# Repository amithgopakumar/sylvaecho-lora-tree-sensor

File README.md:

# SylvaEcho

A solar-powered LoRa sensor that straps to a tree trunk. It listens for pollinators and birds, detects illegal logging, and reports when a tree or slope starts to lean. It runs without mobile coverage, for forest departments, researchers, farms and citizen scientists.

This is an open hardware project for the [EasyEDA Spark 2026](https://oshwlab.com/activities/easyeda-spark-2026) competition. The PCB is designed in EasyEDA Pro.

## What it does

- **Biodiversity by sound.** Every 30 minutes the node wakes for 10 seconds, powers its microphone and scores pollinator buzz (150–400 Hz) and bird activity (1–6 kHz) on the nRF52840.
- **Illegal logging alerts.** A piezo disc on the trunk plate feeds a band-pass filter and a nanopower comparator. Sustained trunk vibration wakes the MCU, which then checks the IMU and three 1-second audio clips for a chainsaw. An alert is sent only when both agree, which cuts false alarms from wind, rain and traffic.
- **Tilt monitoring.** The IMU tracks slow tilt from cutting, tree fall or soil creep.
- **Long range, no SIM.** Reports and alerts go out over LoRa (IN865, EU868 or US915).
- **Sealed setup.** An NFC tap wakes Bluetooth for configuration, so the enclosure never needs opening.

Between listening windows the microphone rail is switched off. The design target is an average current of about 115 µA.

## Hardware

| Function | Part |
|---|---|
| MCU + Bluetooth | Seeed XIAO nRF52840 |
| LoRa radio | Seeed Wio-SX1262 SMT module, up to +22 dBm, U.FL antenna |
| Microphone | Knowles SPH0641LU4H-1 PDM MEMS microphone (bottom port) |
| Motion / tilt | ST LSM6DSOX 6-axis IMU |
| Environment | Bosch BME680 on rev 0.4, BME280 on rev 0.3 (temperature, humidity, pressure) |
| Trunk vibration wake | Piezo disc + TLV7041 nanopower comparator |
| Solar harvesting | TI BQ25570 with MPPT, charging one LiFePO4 cell |
| 3.3 V supply | TI TPS63900 buck-boost |
| I/O expander | TI TCA9534 |
| Mic power switch | TI TPS22917 load switch |
| Expansion | Qwiic (JST-SH) I2C port, test points |

The board is 4-layer, 60 × 45 mm, 1.6 mm FR-4.

### Board versions

The two versions differ only in the environment sensor U5. Both sensors use the same pin order and the same I2C address (0x76), so the schematic, firmware and LoRa report are the same.

| Version | U5 | LCSC part | Footprint | Files |
|---|---|---|---|---|
| Rev 0.4 (current) | Bosch BME680 | C125972 | LGA-8, 3.0 × 3.0 mm, 0.8 mm pitch | `PCB/BME680_rev0.4/` |
| Rev 0.3 | Bosch BME280 | C92489 | LGA-8, 2.5 × 2.5 mm, 0.65 mm pitch | `PCB/BME280_rev0.3/` |

Rev 0.4 was made because the BME280 went out of stock at JLCPCB. The BME680 also has a gas (VOC) sensor; the firmware reads only temperature, humidity and pressure from it.

### Solar panel and battery

- **Battery:** one LiFePO4 cell, for example an IFR18500 (the enclosure size) or an IFR18650. The charger stops at 3.51 V and the system cuts off at about 2.8 V.
- **Solar panel:** 0.3–0.5 W with an open-circuit voltage (Voc) **below 3.1 V**. A 4-cell panel sold as "2 V" (Voc around 2.4–2.6 V) fits. Panels sold as "3 V" usually have a Voc of 3.5–3.6 V, which is too high for this charger setting.

## Companion board SC-1 (battery gauge, security, field sensors)

Rev 0.4 has no battery-voltage line to the MCU, so it cannot report how full the cell is. SC-1 fixes that without changing the main board: it plugs into the Qwiic port, and the battery and piezo cables pass through it.

| Block | Parts | What it does |
|---|---|---|
| Battery gauge | INA219 + 0.22 Ω shunt, ATtiny1616 | Battery voltage and current both ways; charge counting gives the battery % (corrected from the resting voltage at night) |
| Security | ATECC608B | Per-node key that cannot be read out; monotonic counter against replayed packets |
| Field sensors | 5-pin JST-PH: soil-moisture probe, soil NTC, rain gauge; 2-pin cell NTC | Landslide (slope-risk) index together with the main board tilt |
| Trunk sound | MCP6001, 0.5–3.4 kHz, gain 101 | Night listening for wood-boring larvae (red palm weevil) |

- I2C addresses on the main bus: ATtiny1616 0x2A, ATECC608B 0x60. The INA219 sits on the ATtiny's private bus and is powered only while sampling.
- 46 × 21 mm, 2 layers. ICs and connectors on top, 0805 passives on the bottom: everything is hand-solderable.
- Program the ATtiny over UPDI (J9) with a USB-serial adapter (SerialUPDI).
- Files: `PCB/Companion_SC1/` (EasyEDA Pro project, fabrication files, KiCad source and the scripts that generate it).
- v0.2 layout: passives spread with routing channels, every GND pad has its own via to the GND pours, signals routed with EasyEDA's JRouter. Schematic and PCB are linked (all 48 footprints assigned) and EasyEDA's DRC reports no issues.

## Repository layout

```
PCB/
  BME680_rev0.4/
    easyeda/      EasyEDA Pro project, rev 0.4 (schematic and routed PCB)
    fabrication/  Gerber files, JLCPCB BOM and pick-and-place files
  BME280_rev0.3/
    easyeda/      EasyEDA Pro project, rev 0.3
    fabrication/  Gerber files, JLCPCB BOM and pick-and-place files
  Companion_SC1/
    easyeda/      EasyEDA Pro project (.epro2) for the SC-1 add-on board
    fabrication/  Gerber files and the hand-solder BOM
    kicad_source/ Generated KiCad schematic/PCB and schematic PDF
    tools/        Generators and EasyEDA scripts used to build it
  footprints/     Custom KiCad footprints (XIAO SMD, mic, jumper, test point, mounting hole)
  schematic/      Original KiCad schematic (BME280), netlist, BOM and PDF
Firmware/         Zephyr firmware for the XIAO nRF52840 node (both board versions)
  variants/       Environment sensor overlay for each board version
SC1_Firmware/     ATtiny1616 co-processor firmware for the SC-1 add-on (PlatformIO)
Gateway/          XIAO ESP32S3 + Wio-SX1262 gateway: LoRa to USB serial, MQTT and HTTP (PlatformIO, Arduino)
Gateway_zephyr/   Same gateway on Zephyr RTOS: LoRa to USB serial and MQTT (shares Gateway/src/decode.cpp)
Dashboard/
  backend/        Python FastAPI + SQLite: ingest (HTTP/MQTT), history, alerts, settings, live WebSocket
  frontend/       Next.js "Canopy" dashboard: spatial glass UI over the forest
Images/           Renders, block diagram and schematic preview
```

## Building the firmware

The firmware uses Zephyr (nRF Connect SDK).

```
west build -b xiao_ble/nrf52840 Firmware
west flash
```

This builds for rev 0.4 (BME680). For a rev 0.3 board (BME280):

```
west build -b xiao_ble/nrf52840 Firmware -- -DSENSOR=bme280
```

Run `west build -p` after switching between the two so the build directory is regenerated.

Schedule, detection thresholds and LoRa settings are in `Firmware/src/config.h`. The default LoRa channel is 865.0625 MHz (IN865); change it for EU868 or US915. Logs go out over Segger RTT, because the UART pins are used by the microphone.

The node finds the SC-1 add-on at boot (I2C 0x2A) and works the same without it. With SC-1 fitted, every report carries a 24-byte extension (battery, cell and soil temperature, soil moisture, rain totals, borer index), and an SC-1 pulse on WAKE_N (optional TP1 to TP6 wire) sends a `sc1_alert` report for heavy rain, low battery or borer activity.

### SC-1 co-processor (ATtiny1616)

```
cd SC1_Firmware
pio run                                                 # build
pio run -t upload --upload-port /dev/cu.usbserial-XXXX  # flash over UPDI (J9)
```

Flash it with SerialUPDI: a 3.3 V USB-serial adapter with a 4.7k resistor from TX to RX, RX to J9 pin 1 (UPDI), plus 3V3 and GND. The register map is in `SC1_Firmware/src/sc1_regs.h` (the node uses an identical copy). Defaults, all changeable over I2C and saved with command 0xA5: 1000 mAh cell, battery sampled every 60 s, soil and NTCs every 30 min, rain alert at 50 tips (10 mm) per hour, low battery at 15 %, borer listen 20 s after each node report.

Battery % is a coulomb count from INA219 samples, reset at full charge and corrected from the resting LiFePO4 voltage near empty and full. The INA219 is powered only while sampling, so short LoRa transmit peaks between samples are missed; treat the % as an estimate until it has been checked against a bench discharge.

### Gateway (XIAO ESP32S3 + Wio-SX1262)

```
cd Gateway
cp src/secrets.example.h src/secrets.h   # Wi-Fi, MQTT broker and/or HTTP URL
pio run -t upload
pio device monitor                       # one JSON line per packet
```

It listens on the same channel as the node (865.0625 MHz, SF10, BW 125 kHz, CR 4/5, private sync word) and drops repeated packets by node and sequence number. Each report is printed on USB serial, published to MQTT as `sylvaecho/<node>/<type>`, and/or POSTed as JSON to `HTTP_URL`. Leave the MQTT host and HTTP URL empty for serial output only.

### Gateway on Zephyr (alternative)

```
cp Gateway_zephyr/secrets.conf.example Gateway_zephyr/secrets.conf   # Wi-Fi and MQTT
west build -b xiao_esp32s3/esp32s3/procpu Gateway_zephyr
west blobs fetch hal_espressif      # once, for the ESP32 Wi-Fi driver
west flash
```

Same radio settings, JSON output and MQTT topics as the Arduino gateway, using Zephyr's own SX1262 driver (`lora_recv_async`), Wi-Fi management, DHCP and MQTT client. It has no HTTP POST yet. Pins are in `Gateway_zephyr/boards/xiao_esp32s3_esp32s3_procpu.overlay`.

### Report format

19-byte base report (unchanged), with byte 18 = extension flags. When bit 0 is set, the 24-byte SC-1 block follows (43 bytes in total). The full layout is in `Firmware/src/payload.h`; the gateway decoder is `Gateway/src/decode.cpp`.

## Dashboard

```
cd Dashboard/backend
python3 -m venv .venv && .venv/bin/pip install -r requirements.txt
DEMO=1 .venv/bin/uvicorn app:app --port 8000     # DEMO=1 simulates three trees

cd Dashboard/frontend
npm install && npm run dev                      # http://localhost:3000
```

The backend stores every report in SQLite and pushes it to the browser over a WebSocket. Reports arrive from the Arduino gateway's HTTP POST (`HTTP_URL = "http://<pc>:8000/api/ingest"`, optional `INGEST_TOKEN`) or from MQTT (`MQTT_HOST=<broker>` subscribes to `sylvaecho/+/+`, which works with both gateways). Demo data is labelled "Demo data" in the corner and `"demo": true` in the API; leave `DEMO` unset for real nodes.

The front end is a spatial glass window over the forest photo, with mouse parallax and a fluid 1440 x 810 layout (a stacked layout on phones):

- **Tabs:** all trees, or one tree each. Switching wipes the node view and rolls the card titles.
- **Rail:** what the dial shows: slope risk, rain, battery, bird activity, temperature.
- **Dial:** the live value as a mint arc. Drag the white knob to set that metric's alert level (saved on the server). The centre button mutes alerts on this screen.
- **Node view:** the device photo with a live spectrogram drawn from the pollinator, bird and chainsaw scores. Click it to fill the window.
- **Storm watch:** tightens the rain and risk alerts and switches to the rain view.
- **Chainsaw guard:** arm or disarm alerts. A confirmed logging alert turns the card red.
- **Battery:** the SC-1 state of charge, current and cell temperature.
- **Timeline:** drag back through the last day. The forest behind the glass darkens for night hours.
- **Soundscape:** steps through recent highlights: dawn chorus, pollinators, rain, borer clicks and alerts.

Open `http://localhost:3000/?shot` for a flat, still layout for screenshots.

### Security and alerts

- **Signed reports.** Each node signs every packet. It adds a 16-byte trailer: a random boot ID, a counter, and an 8-byte HMAC-SHA256 tag (`Firmware/src/auth.c`). Give each node its own key: put it in `Firmware/secrets.conf` (copy `secrets.conf.example`) and put the same key in `Dashboard/backend/keys.json` (see `keys.example.json`). Both files are git-ignored.
- **What the server does.** The gateway passes the raw packet through, and the server checks the tag against the raw bytes (`Dashboard/backend/protocol.py`). For any node that has a key, it rejects:
  - unsigned packets (HTTP 403);
  - forged or altered packets (403);
  - replayed packets (409): a counter it has already seen, or a packet from an earlier boot.

  Each rejection is logged at `/api/security`, appears on the dashboard as a warning and in the soundscape, and sends a phone alert.
- **Test it.** `.venv/bin/python tools/attack_test.py --node 1` replays, forges and strips a real packet and shows the server rejecting each one. The demo trees sign with fixed, public demo keys; never use those on real nodes.
- **Phone alerts.** Set `NTFY_URL=https://ntfy.sh/<long-random-topic>` (or your own ntfy server, with `NTFY_TOKEN`) and subscribe to the same topic in the ntfy app. You get alerts for:
  - a confirmed chainsaw (while the guard is armed);
  - tree tilt;
  - SC-1 rain, low battery or borer alerts;
  - slope risk crossing its alert level;
  - rejected packets.

  Each kind of alert repeats at most every 10 minutes per tree.
- **Login.** Set `DASH_PASSWORD` to require a password for the dashboard, its API and the live socket. Sign-in tokens last 7 days. `INGEST_TOKEN` separately protects the gateway's `/api/ingest`.
- **HTTPS.** `Dashboard/Caddyfile` serves the dashboard, API and live socket on one HTTPS address. Build the front end with `NEXT_PUBLIC_API=same-origin`. The Caddyfile has not been tested here.
- **Not done yet.** The key is still in node flash. Next step: keep it in the ATECC608B on SC-1 and use its HMAC command and monotonic counter.

The slope-risk index (0-100) combines 24 h and 3-day rain, soil moisture and tree tilt. It is a screening heuristic for the dashboard, not a calibrated landslide model.

## Ordering the board

1. Open `PCB/BME680_rev0.4/easyeda/SylvaEcho_rev0.4_BME680.epro` in EasyEDA Pro (File > Import), or use the files in `PCB/BME680_rev0.4/fabrication/` directly. For the BME280 version use `PCB/BME280_rev0.3/`.
2. PCB: 4 layers, 1.6 mm, lead-free HASL.
3. Assembly (Standard PCBA, top side): upload the `JLC_BOM_*.csv` and `JLC_CPL_*.csv` files from the same folder. JLCPCB flags the SPH0641 microphone (U7) for a manual review after the order is placed.
4. Hand-solder the XIAO nRF52840 (M1) and the Wio-SX1262 module (M2) after assembly. C11 and C12 are optional antenna-matching parts and are not fitted by default.

## Status

| Item | State |
|---|---|
| Schematic | Rev 0.3 |
| PCB layout | Rev 0.4 (BME680) routed and DRC checked; rev 0.3 (BME280) kept |
| Prototype boards | Rev 0.4 at JLCPCB (5 PCBs, 2 assembled); Spark sponsorship coupon approved |
| Companion board SC-1 | v0.2: routed, DRC clean; 5 PCBs and parts ordered (Lion Circuits, Robu, Evelta), boards due early December 2026 |
| MVP | Being built on development boards with the same sensors |
| Firmware | Node: first version plus SC-1 support; detection thresholds are placeholders until the classifier is trained |
| SC-1 firmware | Builds (8.2 KB of 16 KB flash); waiting for boards to test on hardware |
| Gateway firmware | Arduino version builds for the XIAO ESP32S3; decoder checked against the node's packer on a PC. Zephyr version written, not yet built |
| Dashboard | Python backend and Next.js front end run with demo data; waiting for the gateway to feed real reports |
| Field test | Planned |

## License

Apache License 2.0. See [LICENSE](LICENSE).

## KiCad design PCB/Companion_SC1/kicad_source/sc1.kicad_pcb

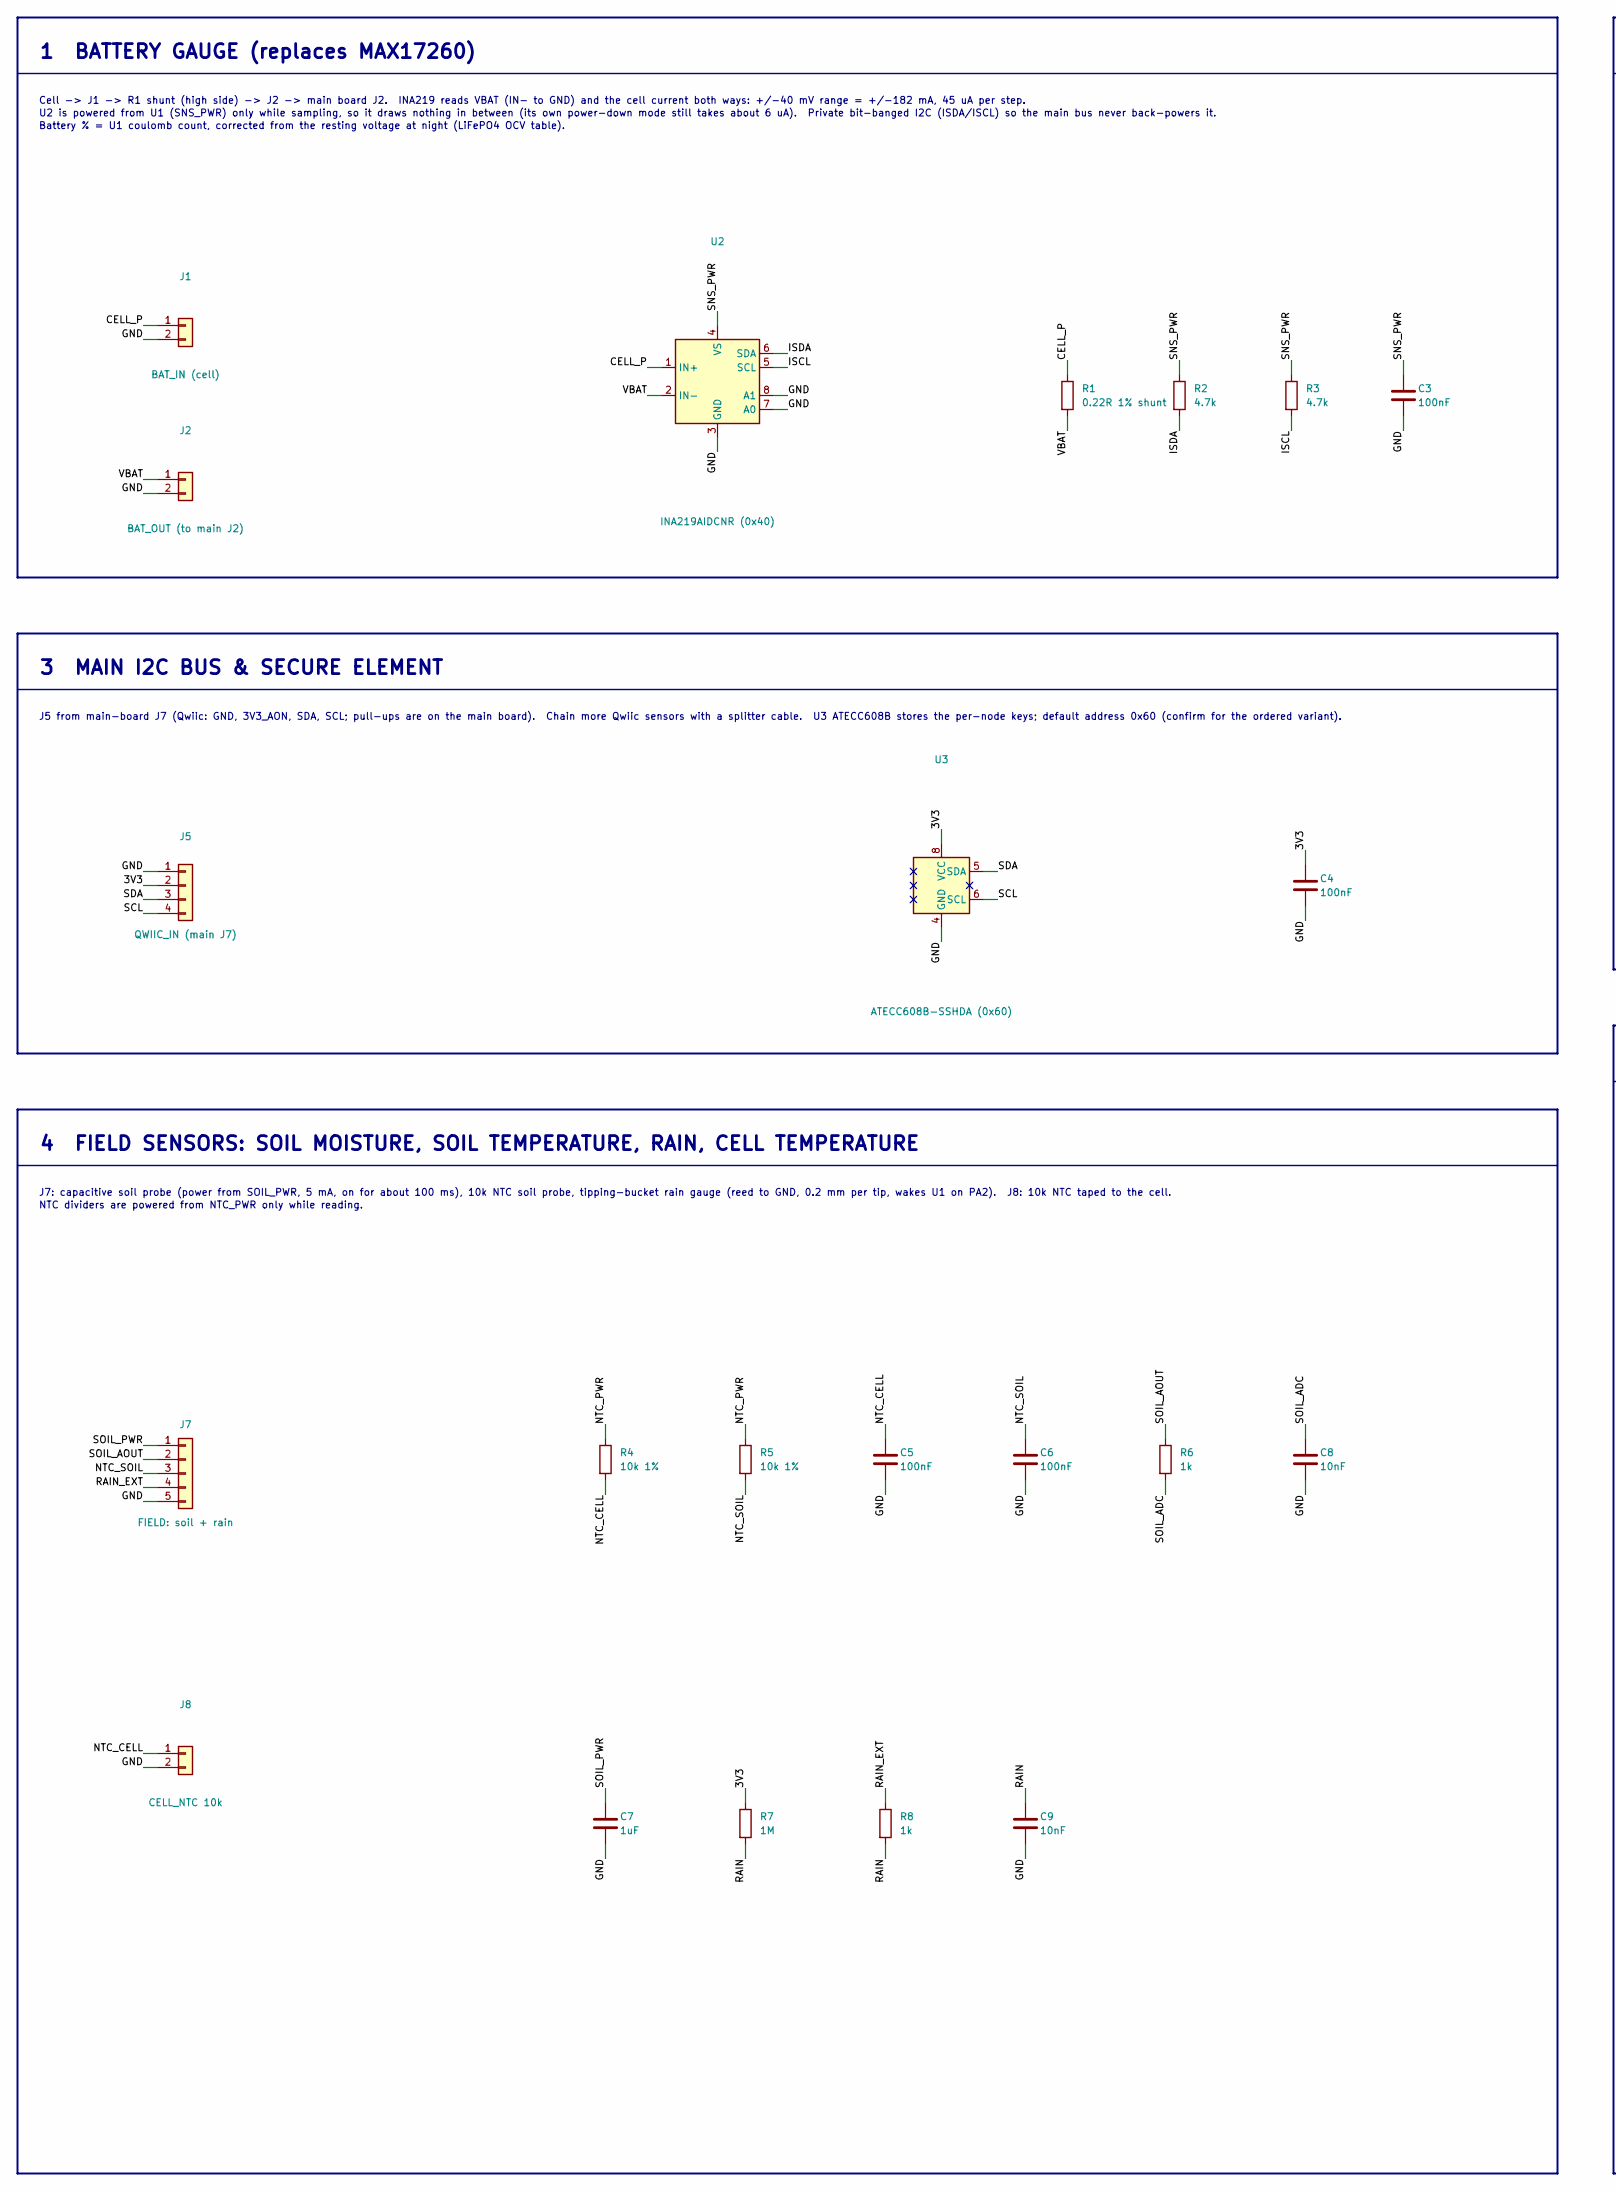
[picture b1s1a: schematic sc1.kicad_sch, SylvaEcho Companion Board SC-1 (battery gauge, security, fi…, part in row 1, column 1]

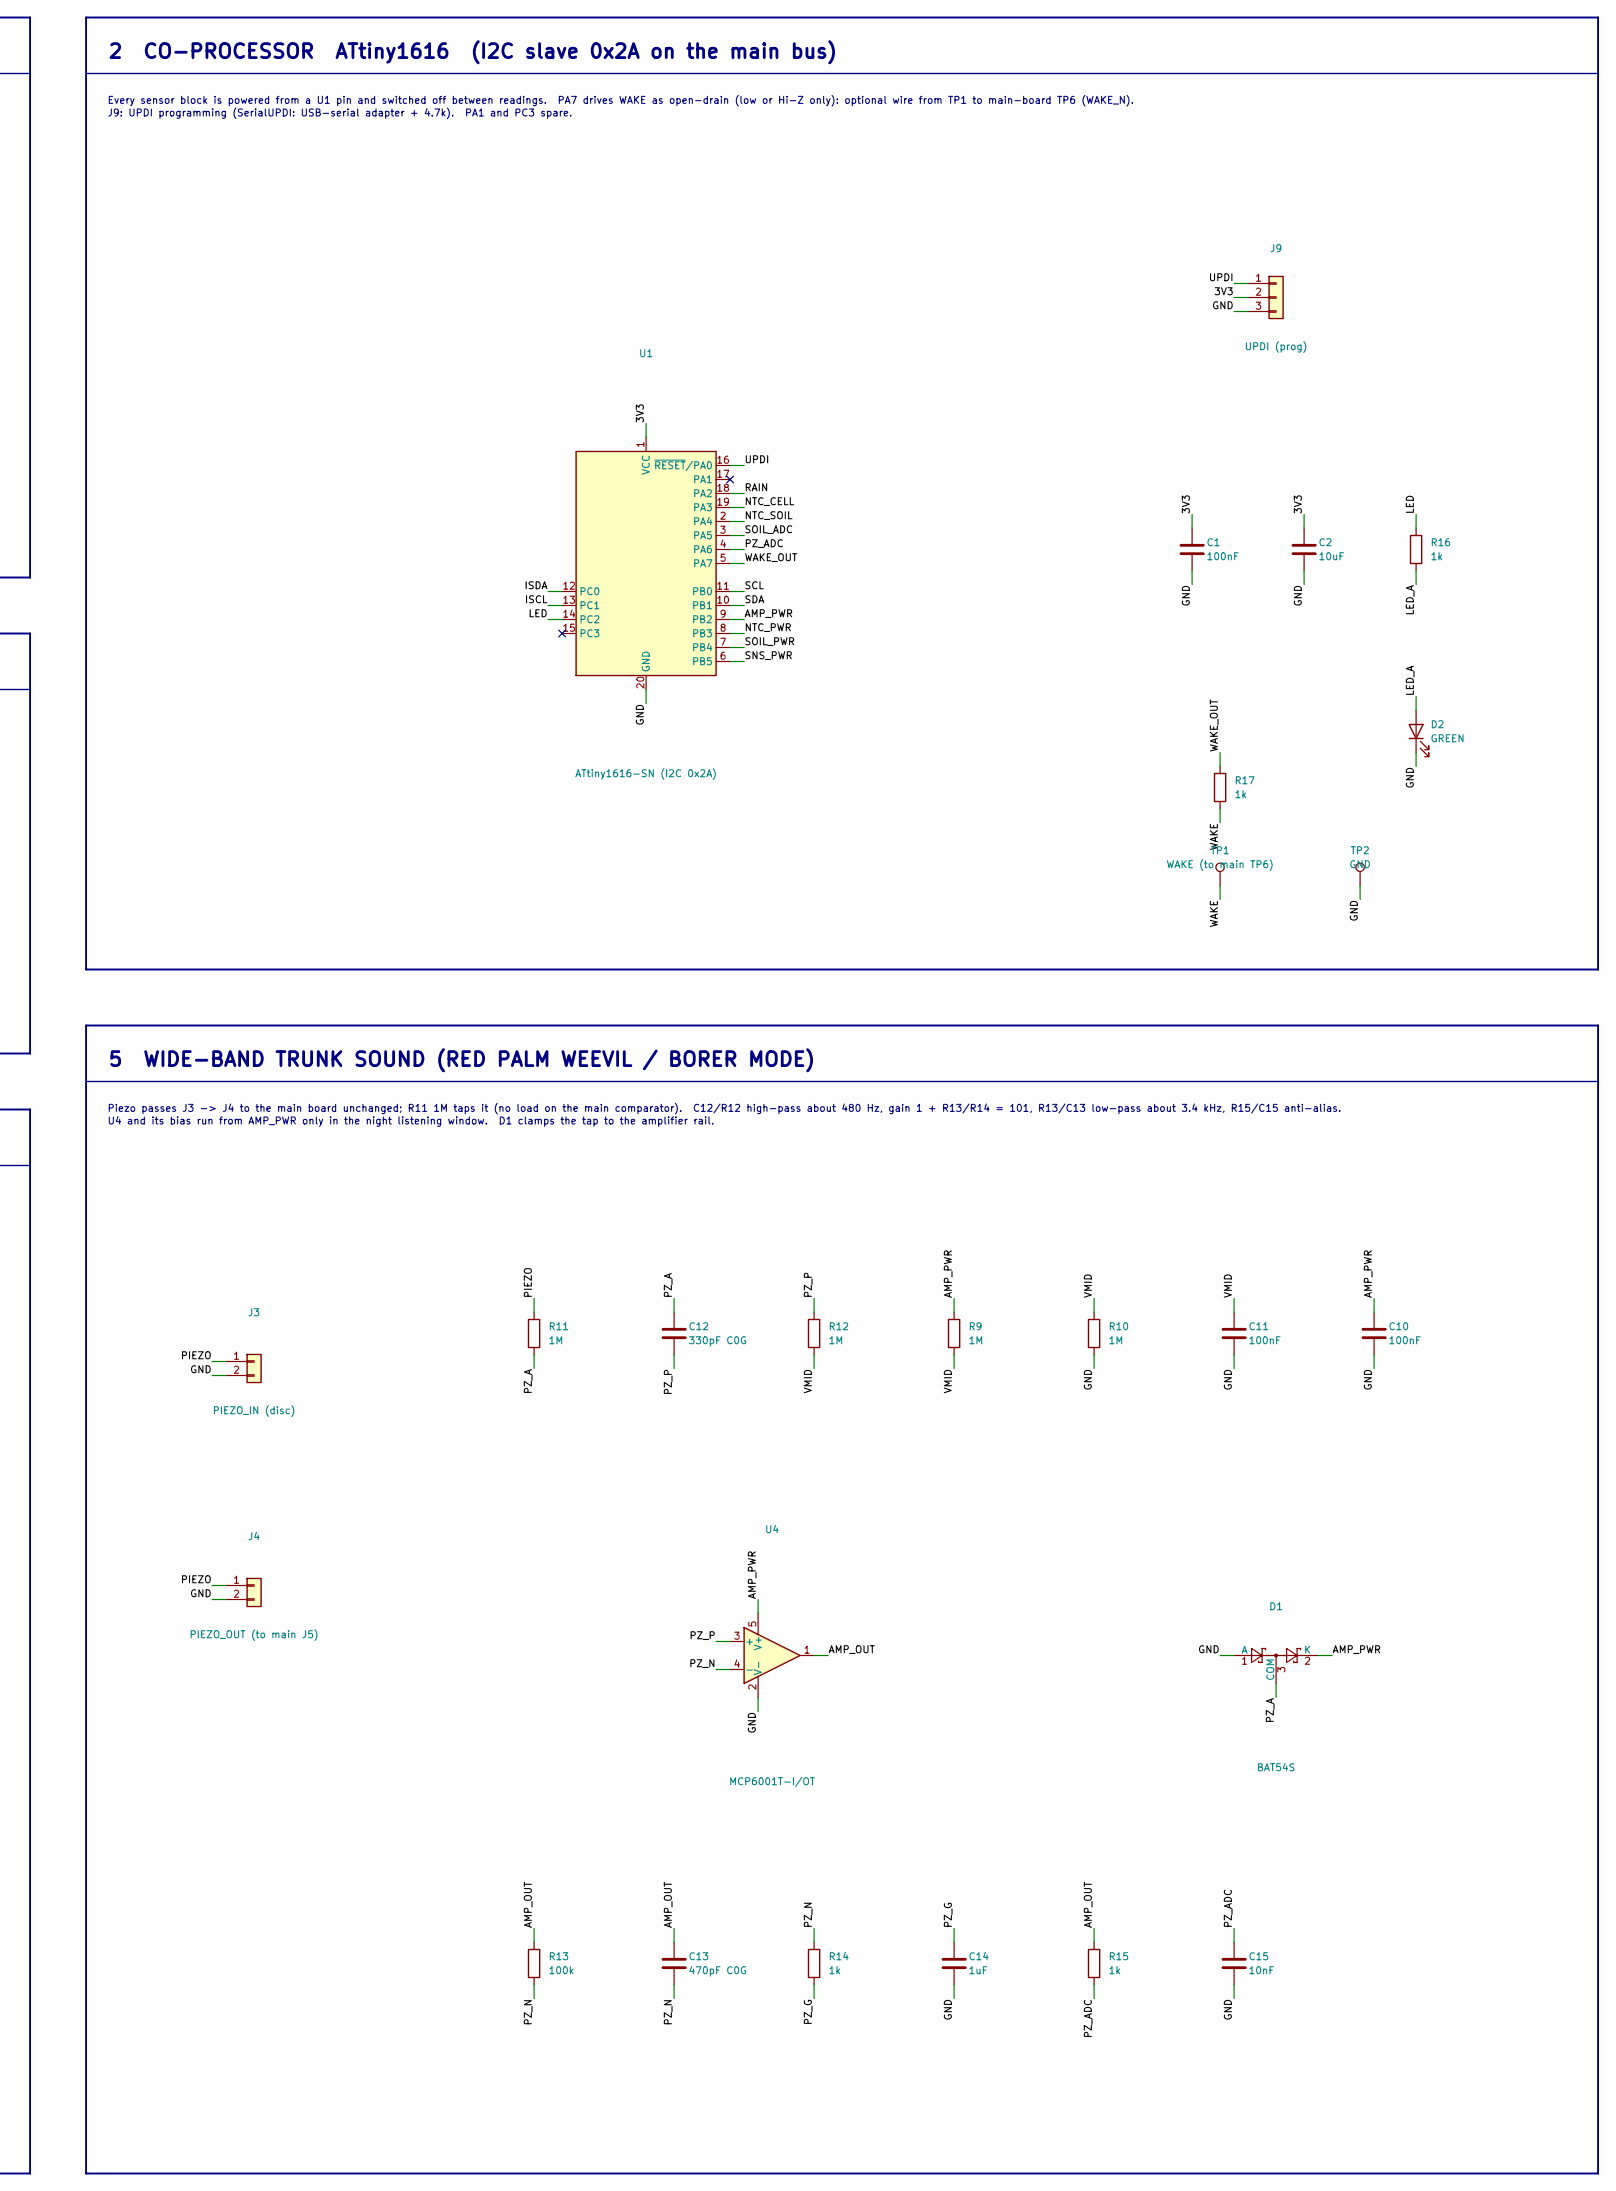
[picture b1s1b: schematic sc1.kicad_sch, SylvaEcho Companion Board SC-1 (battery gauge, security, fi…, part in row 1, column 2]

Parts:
C1, C3, C4, C5, C6, C10, C11: 100nF; C_0805_2012Metric_Pad1.18x1.45mm_HandSolder
C2: 10uF; C_0805_2012Metric_Pad1.18x1.45mm_HandSolder
C7, C14: 1uF; C_0805_2012Metric_Pad1.18x1.45mm_HandSolder
C8, C9, C15: 10nF; C_0805_2012Metric_Pad1.18x1.45mm_HandSolder
C12: 330pF C0G; C_0805_2012Metric_Pad1.18x1.45mm_HandSolder
C13: 470pF C0G; C_0805_2012Metric_Pad1.18x1.45mm_HandSolder
D1: BAT54S; SOT-23_Handsoldering
D2: GREEN; LED_0805_2012Metric_Pad1.15x1.40mm_HandSolder
J1: BAT_IN (cell); JST_PH_B2B-PH-K_1x02_P2.00mm_Vertical
J2: BAT_OUT (to main J2); JST_PH_B2B-PH-K_1x02_P2.00mm_Vertical
J3: PIEZO_IN (disc); JST_PH_B2B-PH-K_1x02_P2.00mm_Vertical
J4: PIEZO_OUT (to main J5); JST_PH_B2B-PH-K_1x02_P2.00mm_Vertical
J5: QWIIC_IN (main J7); JST_SH_SM04B-SRSS-TB_1x04-1MP_P1.00mm_Horizontal
J7: FIELD: soil + rain; JST_PH_B5B-PH-K_1x05_P2.00mm_Vertical
J8: CELL_NTC 10k; JST_PH_B2B-PH-K_1x02_P2.00mm_Vertical
J9: UPDI (prog); PinHeader_1x03_P2.54mm_Vertical
R1: 0.22R 1% shunt; R_0805_2012Metric_Pad1.20x1.40mm_HandSolder
R2, R3: 4.7k; R_0805_2012Metric_Pad1.20x1.40mm_HandSolder
R4, R5: 10k 1%; R_0805_2012Metric_Pad1.20x1.40mm_HandSolder
R6, R8, R14, R15, R16, R17: 1k; R_0805_2012Metric_Pad1.20x1.40mm_HandSolder
R7, R9, R10, R11, R12: 1M; R_0805_2012Metric_Pad1.20x1.40mm_HandSolder
R13: 100k; R_0805_2012Metric_Pad1.20x1.40mm_HandSolder
TP1: WAKE (to main TP6); TestPoint_THTPad_1.5x1.5mm_Drill0.7mm
TP2: GND; TestPoint_THTPad_1.5x1.5mm_Drill0.7mm
U1: ATtiny1616-SN (I2C 0x2A); SOIC-20W_7.5x12.8mm_P1.27mm
U2: INA219AIDCNR (0x40); SOT-23-8_Handsoldering
U3: ATECC608B-SSHDA (0x60); SOIC-8_3.9x4.9mm_P1.27mm
U4: MCP6001T-I/OT; SOT-23-5_HandSoldering

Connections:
3V3: C1.1, C2.1, C4.1, J5.2, J9.2, R7.1, U1.1 (VCC), U3.8 (VCC)
AMP_OUT: C13.1, R13.1, R15.1, U4.1
AMP_PWR: C10.1, D1.2 (K), R9.1, U1.9 (PB2), U4.5 (V+)
CELL_P: J1.1, R1.1, U2.1 (IN+)
GND: C1.2, C2.2, C3.2, C4.2, C5.2, C6.2, C7.2, C8.2, C9.2, C10.2, C11.2, C14.2, C15.2, D1.1 (A), D2.1 (K), J1.2, J2.2, J3.2, J4.2, J5.1, J7.5, J8.2, J9.3, R10.2, TP2.1, U1.20 (GND), U2.3 (GND), U2.7 (A0), U2.8 (A1), U3.4 (GND), U4.2 (V-)
ISCL: R3.2, U1.13 (PC1), U2.5 (SCL)
ISDA: R2.2, U1.12 (PC0), U2.6 (SDA)
LED: R16.1, U1.14 (PC2)
LED_A: D2.2 (A), R16.2
NTC_CELL: C5.1, J8.1, R4.2, U1.19 (PA3)
NTC_PWR: R4.1, R5.1, U1.8 (PB3)
NTC_SOIL: C6.1, J7.3, R5.2, U1.2 (PA4)
PIEZO: J3.1, J4.1, R11.1
PZ_A: C12.1, D1.3 (COM), R11.2
PZ_ADC: C15.1, R15.2, U1.4 (PA6)
PZ_G: C14.1, R14.2
PZ_N: C13.2, R13.2, R14.1, U4.4 (-)
PZ_P: C12.2, R12.1, U4.3 (+)
RAIN: C9.1, R7.2, R8.2, U1.18 (PA2)
RAIN_EXT: J7.4, R8.1
SCL: J5.4, U1.11 (PB0), U3.6 (SCL)
SDA: J5.3, U1.10 (PB1), U3.5 (SDA)
SNS_PWR: C3.1, R2.1, R3.1, U1.6 (PB5), U2.4 (VS)
SOIL_ADC: C8.1, R6.2, U1.3 (PA5)
SOIL_AOUT: J7.2, R6.1
SOIL_PWR: C7.1, J7.1, U1.7 (PB4)
UPDI: J9.1, U1.16 (~RESET/PA0)
VBAT: J2.1, R1.2, U2.2 (IN-)
VMID: C11.1, R9.2, R10.1, R12.2
WAKE: R17.2, TP1.1
WAKE_OUT: R17.1, U1.5 (PA7)

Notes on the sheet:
1 BATTERY GAUGE (replaces MAX17260)
Cell -> J1 -> R1 shunt (high side) -> J2 -> main board J2. INA219 reads VBAT (IN- to GND) and the cell current both ways: +/-40 mV range = +/-182 mA, 45 uA per step.
U2 is powered from U1 (SNS_PWR) only while sampling, so it draws nothing in between (its own power-down mode still takes about 6 uA). Private bit-banged I2C (ISDA/ISCL) so the main bus never back-powers it.
Battery % = U1 coulomb count, corrected from the resting voltage at night (LiFePO4 OCV table).
2 CO-PROCESSOR ATtiny1616 (I2C slave 0x2A on the main bus)
Every sensor block is powered from a U1 pin and switched off between readings. PA7 drives WAKE as open-drain (low or Hi-Z only): optional wire from TP1 to main-board TP6 (WAKE_N).
J9: UPDI programming (SerialUPDI: USB-serial adapter + 4.7k). PA1 and PC3 spare.
3 MAIN I2C BUS & SECURE ELEMENT
J5 from main-board J7 (Qwiic: GND, 3V3_AON, SDA, SCL; pull-ups are on the main board). Chain more Qwiic sensors with a splitter cable. U3 ATECC608B stores the per-node keys; default address 0x60 (confirm for the ordered variant).
4 FIELD SENSORS: SOIL MOISTURE, SOIL TEMPERATURE, RAIN, CELL TEMPERATURE
J7: capacitive soil probe (power from SOIL_PWR, 5 mA, on for about 100 ms), 10k NTC soil probe, tipping-bucket rain gauge (reed to GND, 0.2 mm per tip, wakes U1 on PA2). J8: 10k NTC taped to the cell.
NTC dividers are powered from NTC_PWR only while reading.
5 WIDE-BAND TRUNK SOUND (RED PALM WEEVIL / BORER MODE)
Piezo passes J3 -> J4 to the main board unchanged; R11 1M taps it (no load on the main comparator). C12/R12 high-pass about 480 Hz, gain 1 + R13/R14 = 101, R13/C13 low-pass about 3.4 kHz, R15/C15 anti-alias.
U4 and its bias run from AMP_PWR only in the night listening window. D1 clamps the tap to the amplifier rail.

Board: 2 copper layers, 48 parts (27 on the bottom side), 31 nets, no tracks yet.

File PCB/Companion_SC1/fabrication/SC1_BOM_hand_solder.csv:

Designators,Qty,Value,Footprint,Manufacturer,Part number / description,Side
C12,1,330pF C0G,C_0805_2012Metric_Pad1.18x1.45mm_HandSolder,Any,0805 330pF 50V C0G,Bottom: C12
C13,1,470pF C0G,C_0805_2012Metric_Pad1.18x1.45mm_HandSolder,Any,0805 470pF 50V C0G,Bottom: C13
C2,1,10uF,C_0805_2012Metric_Pad1.18x1.45mm_HandSolder,Any,0805 10uF 16V X5R,Bottom: C2
"C3, C1, C4, C5, C6, C11, C10",7,100nF,C_0805_2012Metric_Pad1.18x1.45mm_HandSolder,Any,0805 100nF 50V X7R,Top: C6; Bottom: C3 C1 C4 C5 C11 C10
"C7, C14",2,1uF,C_0805_2012Metric_Pad1.18x1.45mm_HandSolder,Any,0805 1uF 25V X7R,Bottom: C7 C14
"C8, C9, C15",3,10nF,C_0805_2012Metric_Pad1.18x1.45mm_HandSolder,Any,0805 10nF 50V X7R,Top: C15; Bottom: C8 C9
D1,1,BAT54S,SOT-23_Handsoldering,Nexperia,"BAT54S,215",Top: D1
D2,1,GREEN,LED_0805_2012Metric_Pad1.15x1.40mm_HandSolder,Lite-On,LTST-C170KGKT (green 0805),Top: D2
J1,1,BAT_IN (cell),JST_PH_B2B-PH-K_1x02_P2.00mm_Vertical,JST,B2B-PH-K-S(LF)(SN),Top: J1
J2,1,BAT_OUT (to main J2),JST_PH_B2B-PH-K_1x02_P2.00mm_Vertical,JST,B2B-PH-K-S(LF)(SN),Top: J2
J3,1,PIEZO_IN (disc),JST_PH_B2B-PH-K_1x02_P2.00mm_Vertical,JST,B2B-PH-K-S(LF)(SN),Top: J3
J4,1,PIEZO_OUT (to main J5),JST_PH_B2B-PH-K_1x02_P2.00mm_Vertical,JST,B2B-PH-K-S(LF)(SN),Top: J4
J5,1,QWIIC_IN (main J7),JST_SH_SM04B-SRSS-TB_1x04-1MP_P1.00mm_Horizontal,JST,SM04B-SRSS-TB(LF)(SN),Top: J5
J7,1,FIELD: soil + rain,JST_PH_B5B-PH-K_1x05_P2.00mm_Vertical,JST,B5B-PH-K-S(LF)(SN),Top: J7
J8,1,CELL_NTC 10k,JST_PH_B2B-PH-K_1x02_P2.00mm_Vertical,JST,B2B-PH-K-S(LF)(SN),Top: J8
J9,1,UPDI (prog),PinHeader_1x03_P2.54mm_Vertical,Generic,1x3 pin header 2.54 mm,Top: J9
R1,1,0.22R 1% shunt,R_0805_2012Metric_Pad1.20x1.40mm_HandSolder,Yageo,RL0805FR-070R22L (0.22R 1% 1/8W),Top: R1
R13,1,100k,R_0805_2012Metric_Pad1.20x1.40mm_HandSolder,Yageo,RC0805FR-07100KL (1%),Bottom: R13
"R16, R17, R6, R8, R14, R15",6,1k,R_0805_2012Metric_Pad1.20x1.40mm_HandSolder,Yageo,RC0805FR-071KL (1%),Top: R17; Bottom: R16 R6 R8 R14 R15
"R2, R3",2,4.7k,R_0805_2012Metric_Pad1.20x1.40mm_HandSolder,Yageo,RC0805FR-074.7KL (1%),Bottom: R2 R3
"R4, R5",2,10k 1%,R_0805_2012Metric_Pad1.20x1.40mm_HandSolder,Yageo,RC0805FR-0710KL (1%),Bottom: R4 R5
"R7, R11, R12, R9, R10",5,1M,R_0805_2012Metric_Pad1.20x1.40mm_HandSolder,Yageo,RC0805FR-071ML (1%),Top: R10; Bottom: R7 R11 R12 R9
TP1,1,WAKE (to main TP6),TestPoint_THTPad_1.5x1.5mm_Drill0.7mm,-,THT pad (wire to main TP6),Top: TP1
TP2,1,GND,TestPoint_THTPad_1.5x1.5mm_Drill0.7mm,-,THT pad,Top: TP2
U1,1,ATtiny1616-SN (I2C 0x2A),SOIC-20W_7.5x12.8mm_P1.27mm,Microchip,ATTINY1616-SN,Top: U1
U2,1,INA219AIDCNR (0x40),SOT-23-8_Handsoldering,Texas Instruments,INA219AIDCNR,Top: U2
U3,1,ATECC608B-SSHDA (0x60),SOIC-8_3.9x4.9mm_P1.27mm,Microchip,ATECC608B-SSHDA-T,Top: U3
U4,1,MCP6001T-I/OT,SOT-23-5_HandSoldering,Microchip,MCP6001T-I/OT,Top: U4

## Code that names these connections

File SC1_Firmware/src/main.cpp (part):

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 *
 * The co-processor sleeps in power-down most of the time. It wakes on:
 *   - the RTC periodic interrupt (1 s): time keeping, scheduled sampling
 *   - a rain-gauge tip on PA2 (fully asynchronous pin)
 *   - its own I2C address on the main bus (TWI slave address match)
 *
 * Pin map (SC-1 v0.2 schematic)
 *   PA2  RAIN       reed switch to GND, 1M pull-up, 10 nF
 *   PA3  NTC_CELL   AIN3, 10k NTC to GND, 10k to NTC_PWR
 *   PA4  NTC_SOIL   AIN4, same divider
 *   PA5  SOIL_ADC   AIN5, capacitive soil probe output
 *   PA6  PZ_ADC     AIN6, piezo amplifier output (mid-rail biased)
 *   PA7  WAKE_OUT   open-drain pulse to the main-board WAKE_N (optional TP1 wire)
 *   PB5  SNS_PWR    INA219 supply and its I2C pull-ups
 *   PB4  SOIL_PWR   soil probe supply
 *   PB3  NTC_PWR    NTC divider supply
 *   PB2  AMP_PWR    MCP6001 amplifier supply
 *   PB1  SDA, PB0 SCL   main I2C bus (slave 0x2A)
 *   PC0  ISDA, PC1 ISCL private bit-banged I2C to the INA219 (0x40)
 *   PC2  LED
 *   PA0  UPDI
 */
#include <Arduino.h>
#include <Wire.h>
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#include "sc1_regs.h"

/* ------------------------------------------------------------- pins */
#define P_RAIN      PIN_PA2
#define P_NTC_CELL  PIN_PA3
#define P_NTC_SOIL  PIN_PA4
#define P_SOIL      PIN_PA5
#define P_PZ        PIN_PA6
#define P_WAKE      PIN_PA7
#define P_SNS_PWR   PIN_PB5
#define P_SOIL_PWR  PIN_PB4
#define P_NTC_PWR   PIN_PB3
#define P_AMP_PWR   PIN_PB2
#define P_ISDA      PIN_PC0
#define P_ISCL      PIN_PC1
#define P_LED       PIN_PC2

/* ---------------------------------------------------- battery model */
#define SHUNT_MOHM          220     /* R1 0.22 ohm */
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	return ok;
}

/* Power the INA219 for one triggered conversion. Both pins are pulled up to SNS_PWR,
 * so they stay as inputs (low output latch) while the sensor is off: no back-powering. */
static bool ina_measure(int16_t *shunt_10uv, uint16_t *bus_mv)
{
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	digitalWrite(P_ISDA, LOW);    /* open-drain emulation: OUT=0, toggle DIR */
	digitalWrite(P_ISCL, LOW);
	pinMode(P_RAIN, INPUT);       /* R7 is the pull-up */
	PORTA.PIN2CTRL = PORT_ISC_FALLING_gc; /* PA2 is fully asynchronous: wakes from power-down */

	/* Unused pins (PA1, PC3): input with pull-up so they do not float. */
	pinMode(PIN_PA1, INPUT_PULLUP);
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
